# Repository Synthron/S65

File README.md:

# S65xx Computer System

Yet another 8bit Retro Computer

Completely bloated, overkill and fully hackable!

## ToDo

- [x] Finish Hardware
- Software
  - [ ] WozMon
    - [x] Implement Serial IO
    - [x] Implement Input Buffer
    - [ ] extended for block write
  - [ ] Kernel Functions
    - [ ] General SysCalls
    - [ ] Hardware Drivers
  - [x] RAM-Kernel
  - [x] Basic
  - [x] EhBasic
  - [ ] File System
  - [ ] Operating System
- Hardware
  - [ ] order PCBs
  - [ ] order parts
  - [ ] solder together

## Hardware

- Modules
  - [x] Backplane Bus
  - [x] CPU
  - [x] ROM
  - [x] RAM
  - [x] Bank/IRQ
  - [x] LCD/IRQ
  - [x] SIO
  - [x] PIO
  - [x] User Ports
  - [x] IDE
  - [x] Simple-IDE
  - [x] CF
  - [x] SID
  - [x] Addr + RTC + Clock
  - [x] Prototyping Board
  - [x] LPT Interface
  - [x] MyCPU Graphics Unit Interface

## Software Brainstorm

- EhBasic
  - maybe Microsoft Basic? See Ben Eater
    - both in different banks
- WozMon Main Boot
- Serial Program Bootloader
- File System (FAT?)
- DOS-Like UI

boot routine:

- selftest
  - RAM Check
  - ROM Check + version
- Load Kernel functions to RAM
- Start Monitor

## Memory Map

General:

| Start | End  | Usage      | Size   |
|-------|------|------------|--------|
| 0000  | 7FFF | RAM        | 32.768 |
| 8000  | BEFF | RAM Banked | 16.128 |
| BF00  | BFFF | IO Space   |    256 |
| C000  | FFFF | ROM Banked | 16.384 |

IO Space:

| Start | End  | Usage         |Size|
|-------|------|---------------|----|
| BF00  | BF07 | Bank & IRQ    | 8  |
| BF08  | BF0F | TPI IDE       | 8  |
| BF10  | BF12 | LPT           | 2  |
| BF13  | BF14 | --- (LPT2)    | 2  |
| BF14  | BF16 | MyCPU VGA     | 3  |
| BF17  | BF1B | ---           | 5  |
| BF1C  | BF1F | PIA LEDs      | 4  |
| BF20  | BF2F | VIA 1 LCD IRQ | 16 |
| BF30  | BF3F | VIA 2         | 16 |
| BF40  | BF4F | VIA 3         | 16 |
| BF50  | BF53 | ACIA 1        | 4  |
| BF54  | BF57 | ACIA 2        | 4  |
| BF58  | BF5B | --- (ACIA 3)  | 4  |
| BF5C  | BF5F | --- (ACIA 4)  | 4  |
| BF60  | BF7F | SID 8580      | 32 |
| BF80  | BF87 | Simple IDE    | 8  |
| BF88  | BF8F | CF Card       | 8  |
| BF90  | BF9F | RTC           | 16 |
| BFA0  | BFFF | ---           | 96 |

## Interrupts

The TPI Chip for the memory banks also functions as a priority interrupt controller, providing 5 seperate interrupt lines.  
IRQ_0 is further divided into 8 lines for communication modules, giving an overall of 14 available IRQ-Lines.  

These are currently used as follows:

- IRQ -> TPI
  - IRQ_0 -> VIA0
    - IRQ_0.0 -> ACIA0
    - IRQ_0.1 -> ACIA1
    - IRQ_0.2 -> ACIA2
    - IRQ_0.3 -> ACIA3
    - IRQ_0.4 -> RTC
    - IRQ_0.5 -> ---
    - IRQ_0.6 -> ---
    - IRQ_0.7 -> ---
  - IRQ_1 -> VIA1
  - IRQ_2 -> VIA2
  - IRQ_3 -> ---
  - IRQ_4 -> ---
- NMI -> ---

Note that the NMI is connected to a push button on the bus board.

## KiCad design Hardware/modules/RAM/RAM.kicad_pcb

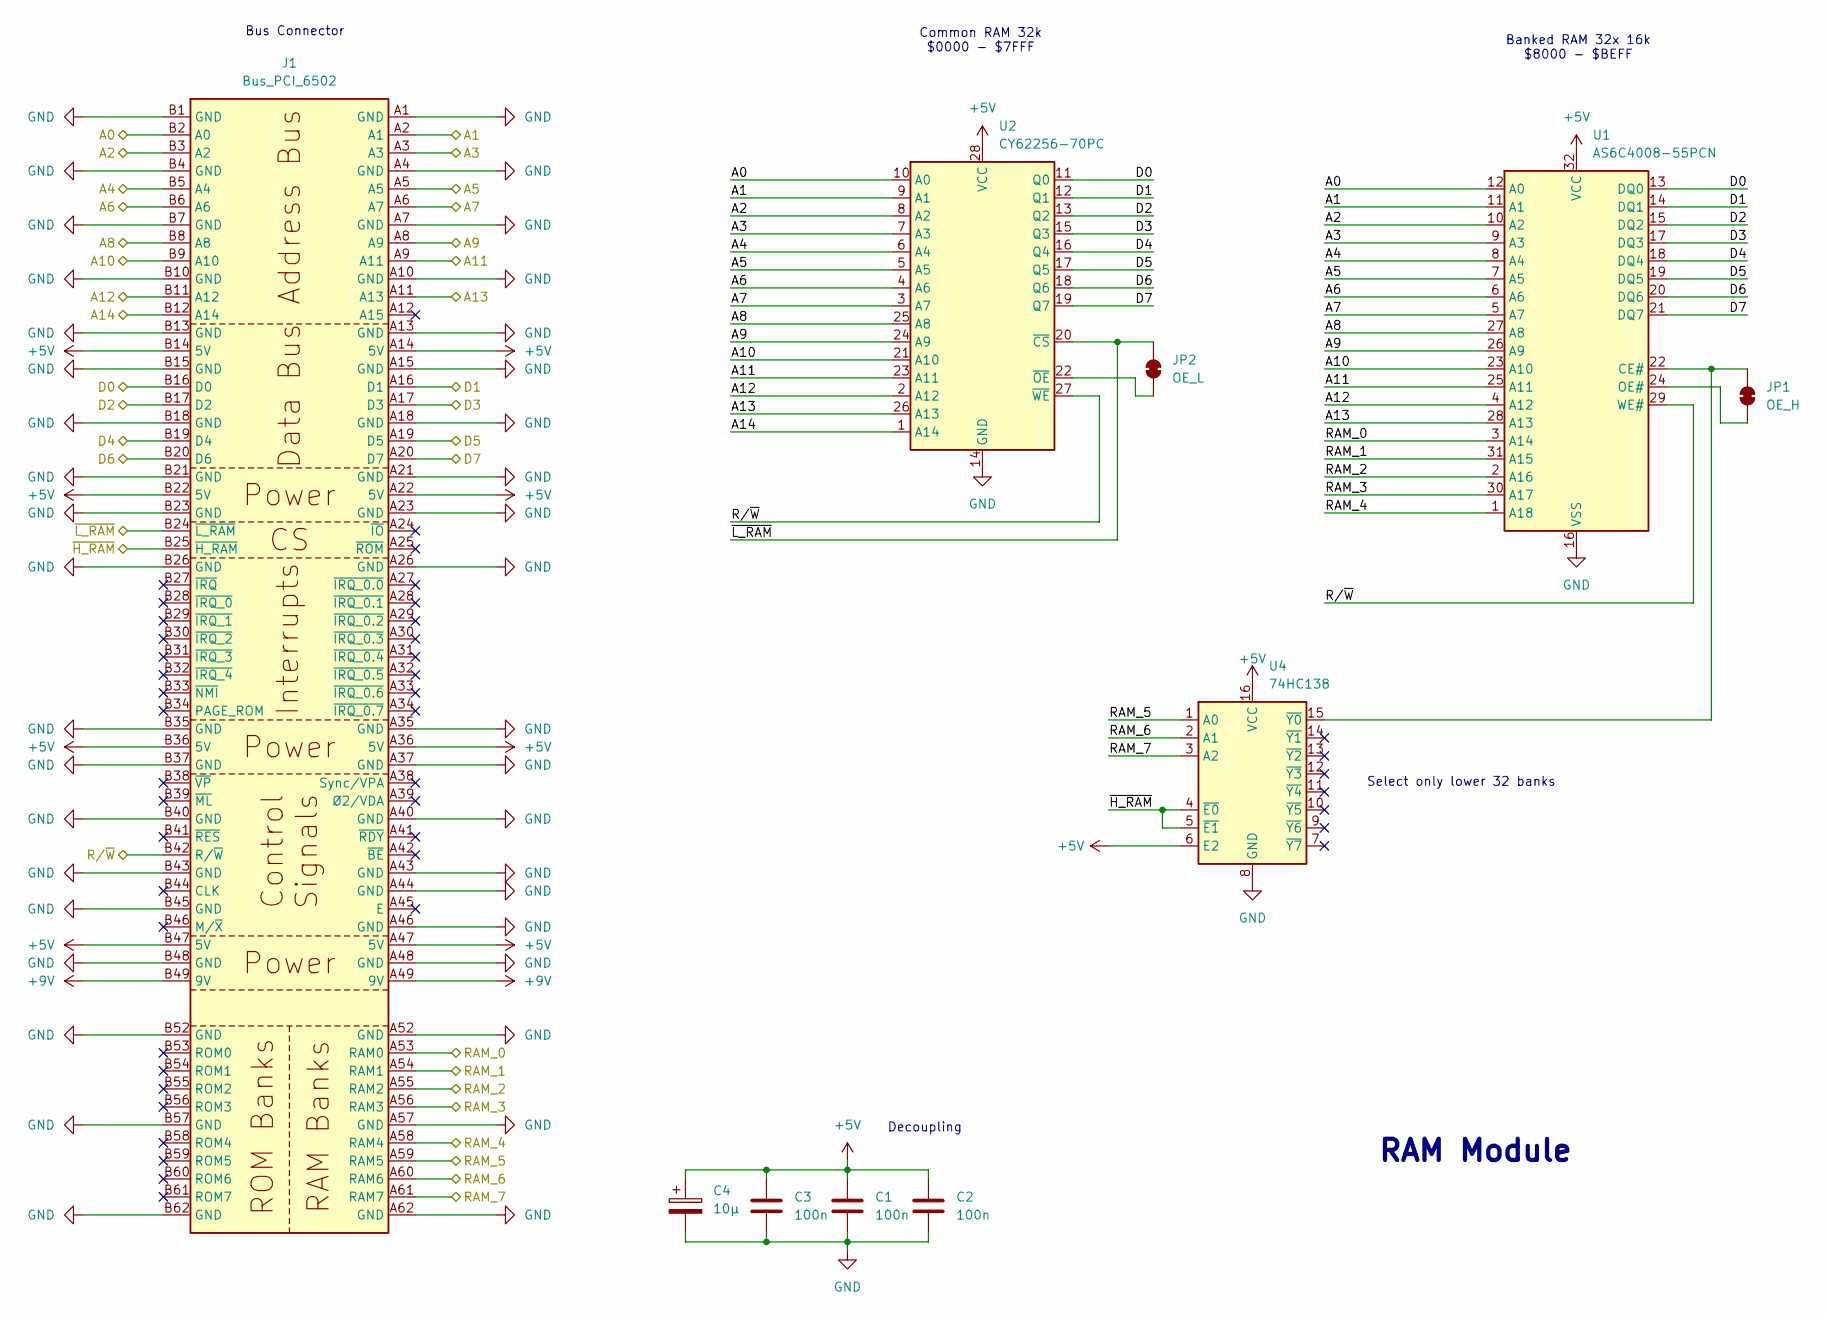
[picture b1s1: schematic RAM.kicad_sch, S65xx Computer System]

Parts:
C1, C2, C3: 100n; C_0805_2012Metric
C4: 10µ; CP_Radial_D5.0mm_P2.50mm
J1: Bus_PCI_6502; BUS_PCI
JP1: OE_H; SolderJumper-2_P1.3mm_Bridged_RoundedPad1.0x1.5mm
JP2: OE_L; SolderJumper-2_P1.3mm_Bridged_RoundedPad1.0x1.5mm
U1: AS6C4008-55PCN; DIP-32_W15.24mm
U2: CY62256-70PC; DIP-28_W15.24mm
U4: 74HC138; DIP-16_W7.62mm

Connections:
+5V: C1.1, C2.1, C3.1, C4.1, J1.A14 (5V), J1.A22 (5V), J1.A36 (5V), J1.A47 (5V), J1.B14 (5V), J1.B22 (5V), J1.B36 (5V), J1.B47 (5V), U1.32 (VCC), U2.28 (VCC), U4.6 (E2), U4.16 (VCC)
+9V: J1.A49 (9V), J1.B49 (9V)
/A0: J1.B2 (A0), U1.12 (A0), U2.10 (A0)
/A1: J1.A2 (A1), U1.11 (A1), U2.9 (A1)
/A2: J1.B3 (A2), U1.10 (A2), U2.8 (A2)
/A3: J1.A3, U1.9 (A3), U2.7 (A3)
/A4: J1.B5 (A4), U1.8 (A4), U2.6 (A4)
/A5: J1.A5, U1.7 (A5), U2.5 (A5)
/A6: J1.B6 (A6), U1.6 (A6), U2.4 (A6)
/A7: J1.A6 (A7), U1.5 (A7), U2.3 (A7)
/A8: J1.B8 (A8), U1.27 (A8), U2.25 (A8)
/A9: J1.A8 (A9), U1.26 (A9), U2.24 (A9)
/A10: J1.B9 (A10), U1.23 (A10), U2.21 (A10)
/A11: J1.A9 (A11), U1.25 (A11), U2.23 (A11)
/A12: J1.B11 (A12), U1.4 (A12), U2.2 (A12)
/A13: J1.A11 (A13), U1.28 (A13), U2.26 (A13)
/A14: J1.B12 (A14), U2.1 (A14)
/D0: J1.B16 (D0), U1.13 (DQ0), U2.11 (Q0)
/D1: J1.A16 (D1), U1.14 (DQ1), U2.12 (Q1)
/D2: J1.B17 (D2), U1.15 (DQ2), U2.13 (Q2)
/D3: J1.A17 (D3), U1.17 (DQ3), U2.15 (Q3)
/D4: J1.B19 (D4), U1.18 (DQ4), U2.16 (Q4)
/D5: J1.A19 (D5), U1.19 (DQ5), U2.17 (Q5)
/D6: J1.B20 (D6), U1.20 (DQ6), U2.18 (Q6)
/D7: J1.A20 (D7), U1.21 (DQ7), U2.19 (Q7)
/RAM_0: J1.A53 (RAM0), U1.3 (A14)
/RAM_1: J1.A54 (RAM1), U1.31 (A15)
/RAM_2: J1.A55 (RAM2), U1.2 (A16)
/RAM_3: J1.A56 (RAM3), U1.30 (A17)
/RAM_4: J1.A58 (RAM4), U1.1 (A18)
/RAM_5: J1.A59 (RAM5), U4.1 (A0)
/RAM_6: J1.A60 (RAM6), U4.2 (A1)
/RAM_7: J1.A61 (RAM7), U4.3 (A2)
/R/~W: J1.B42 (R/~W), U1.29 (WE#), U2.27 (~WE)
/~H_RAM: J1.B25 (~H_RAM), U4.4 (~E0), U4.5 (~E1)
/~L_RAM: J1.B24 (~L_RAM), JP2.2 (B), U2.20 (~CS)
GND: C1.2, C2.2, C3.2, C4.2, J1.A1 (GND), J1.A4 (GND), J1.A7 (GND), J1.A10 (GND), J1.A13 (GND), J1.A15 (GND), J1.A18 (GND), J1.A21 (GND), J1.A23 (GND), J1.A26 (GND), J1.A35 (GND), J1.A37 (GND), J1.A40 (GND), J1.A43 (GND), J1.A44 (GND), J1.A46 (GND), J1.A48 (GND), J1.A52 (GND), J1.A57 (GND), J1.A62 (GND), J1.B1 (GND), J1.B4 (GND), J1.B7 (GND), J1.B10 (GND), J1.B13 (GND), J1.B15 (GND), J1.B18 (GND), J1.B21 (GND), J1.B23 (GND), J1.B26 (GND), J1.B35 (GND), J1.B37 (GND), J1.B40 (GND), J1.B43 (GND), J1.B45 (GND), J1.B48 (GND), J1.B52 (GND), J1.B57 (GND), J1.B62 (GND), U1.16 (VSS), U2.14 (GND), U4.8 (GND)
unnamed: JP1.1 (A), U1.24 (OE#)
unnamed: JP1.2 (B), U1.22 (CE#), U4.15 (~Y0)
unnamed: JP2.1 (A), U2.22 (~OE)

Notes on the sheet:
Common RAM 32k $0000 - $7FFF
RAM Module
Bus Connector
Select only lower 32 banks
Decoupling
Banked RAM 32x 16k $8000 - $BEFF

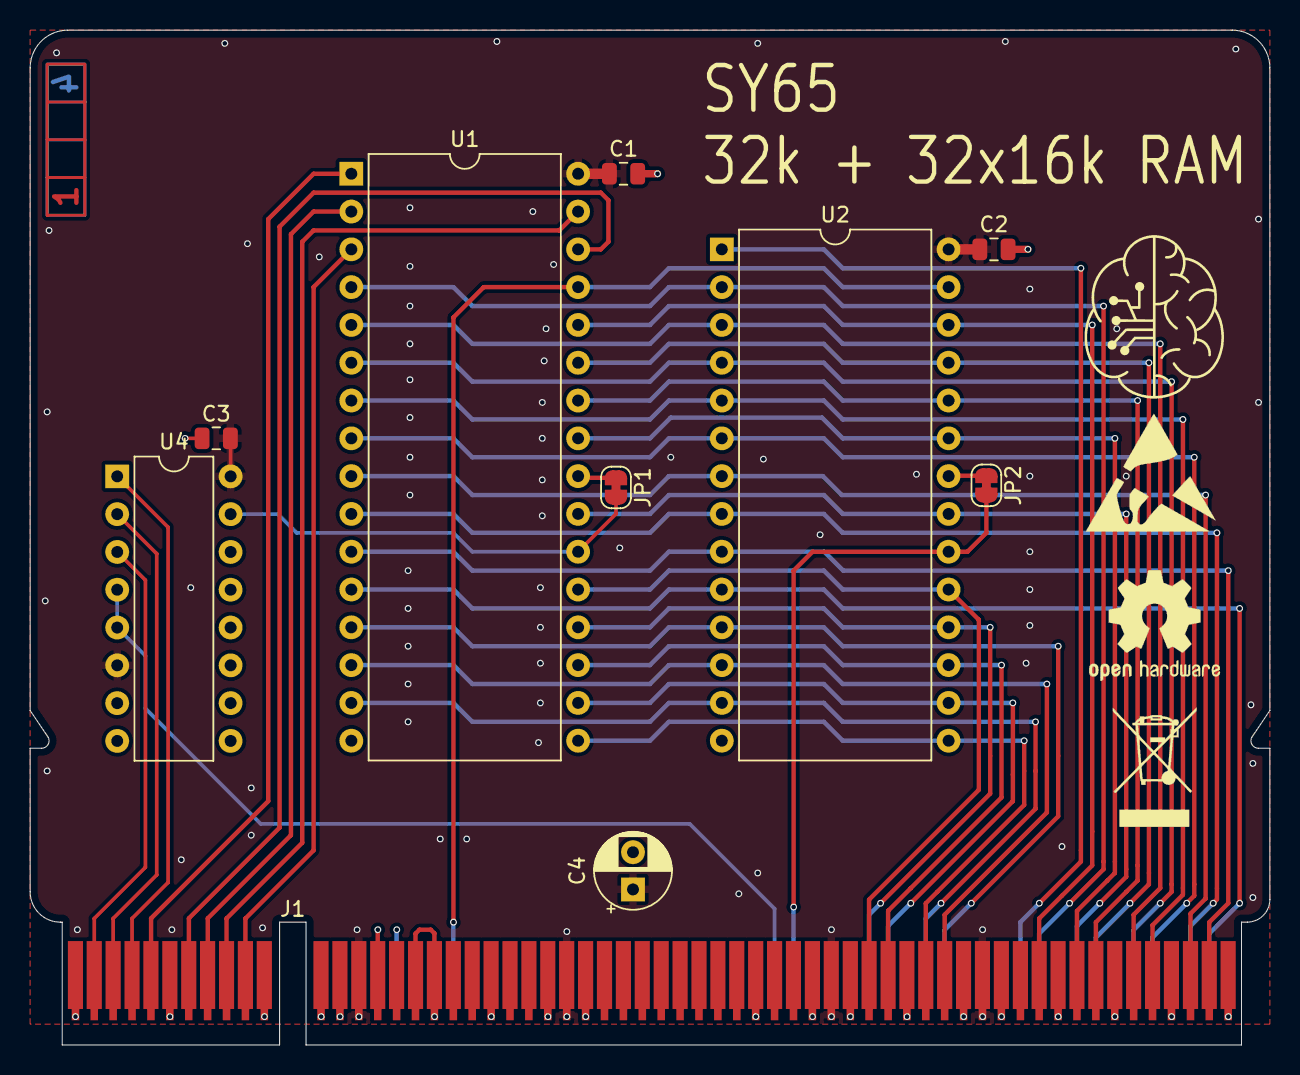
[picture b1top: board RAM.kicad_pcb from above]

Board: 4 copper layers, 83.3 x 68.2 mm, 11 parts (1 on the bottom side), 40 nets.

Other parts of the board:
Ref**: Val**; ladder_4

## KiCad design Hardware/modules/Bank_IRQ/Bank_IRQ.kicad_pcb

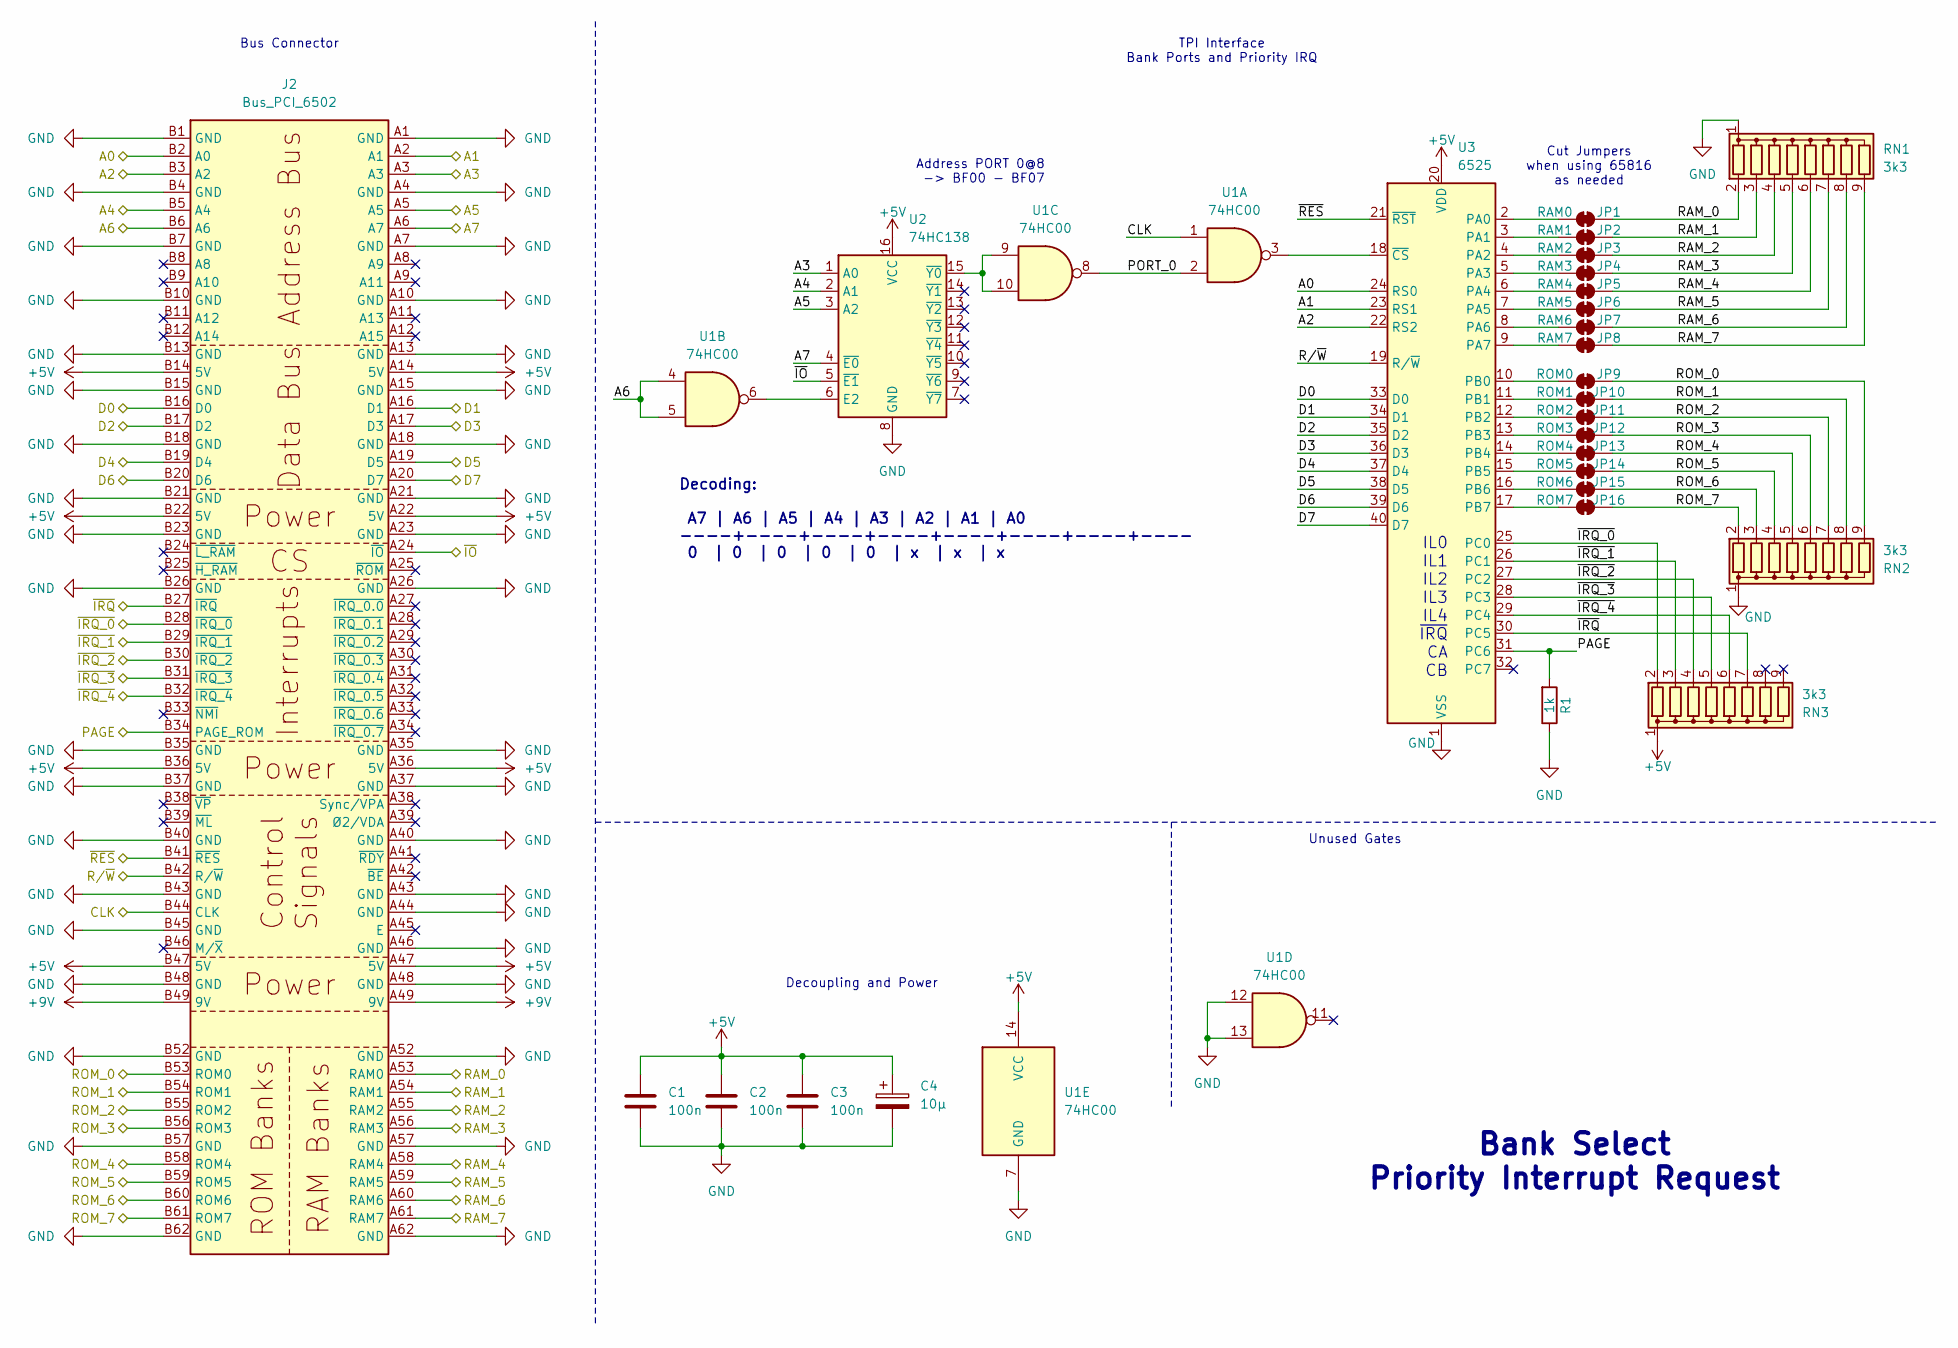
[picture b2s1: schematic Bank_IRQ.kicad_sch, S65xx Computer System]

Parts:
C1, C2, C3: 100n; C_0805_2012Metric
C4: 10µ; CP_Radial_D5.0mm_P2.50mm
J2: Bus_PCI_6502; BUS_PCI
JP1: RAM0; SolderJumper-2_P1.3mm_Bridged_RoundedPad1.0x1.5mm
JP2: RAM1; SolderJumper-2_P1.3mm_Bridged_RoundedPad1.0x1.5mm
JP3: RAM2; SolderJumper-2_P1.3mm_Bridged_RoundedPad1.0x1.5mm
JP4: RAM3; SolderJumper-2_P1.3mm_Bridged_RoundedPad1.0x1.5mm
JP5: RAM4; SolderJumper-2_P1.3mm_Bridged_RoundedPad1.0x1.5mm
JP6: RAM5; SolderJumper-2_P1.3mm_Bridged_RoundedPad1.0x1.5mm
JP7: RAM6; SolderJumper-2_P1.3mm_Bridged_RoundedPad1.0x1.5mm
JP8: RAM7; SolderJumper-2_P1.3mm_Bridged_RoundedPad1.0x1.5mm
JP9: ROM0; SolderJumper-2_P1.3mm_Bridged_RoundedPad1.0x1.5mm
JP10: ROM1; SolderJumper-2_P1.3mm_Bridged_RoundedPad1.0x1.5mm
JP11: ROM2; SolderJumper-2_P1.3mm_Bridged_RoundedPad1.0x1.5mm
JP12: ROM3; SolderJumper-2_P1.3mm_Bridged_RoundedPad1.0x1.5mm
JP13: ROM4; SolderJumper-2_P1.3mm_Bridged_RoundedPad1.0x1.5mm
JP14: ROM5; SolderJumper-2_P1.3mm_Bridged_RoundedPad1.0x1.5mm
JP15: ROM6; SolderJumper-2_P1.3mm_Bridged_RoundedPad1.0x1.5mm
JP16: ROM7; SolderJumper-2_P1.3mm_Bridged_RoundedPad1.0x1.5mm
R1: 1k; R_0805_2012Metric
RN1, RN2, RN3: 3k3; R_Array_SIP9
U1: 74HC00; DIP-14_W7.62mm_LongPads
U2: 74HC138; DIP-16_W7.62mm_LongPads
U3: 6525; DIP-40_W15.24mm

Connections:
+5V: C1.1, C2.1, C3.1, C4.1, J2.A14 (5V), J2.A22 (5V), J2.A36 (5V), J2.A47 (5V), J2.B14 (5V), J2.B22 (5V), J2.B36 (5V), J2.B47 (5V), RN3.1 (common), U1.14 (VCC), U2.16 (VCC), U3.20 (VDD)
+9V: J2.A49 (9V), J2.B49 (9V)
/A0: J2.B2 (A0), U3.24 (RS0)
/A1: J2.A2 (A1), U3.23 (RS1)
/A2: J2.B3 (A2), U3.22 (RS2)
/A3: J2.A3, U2.1 (A0)
/A4: J2.B5 (A4), U2.2 (A1)
/A5: J2.A5, U2.3 (A2)
/A6: J2.B6 (A6), U1.4, U1.5
/A7: J2.A6 (A7), U2.4 (~E0)
/CLK: J2.B44 (CLK), U1.1
/D0: J2.B16 (D0), U3.33 (D0)
/D1: J2.A16 (D1), U3.34 (D1)
/D2: J2.B17 (D2), U3.35 (D2)
/D3: J2.A17 (D3), U3.36 (D3)
/D4: J2.B19 (D4), U3.37 (D4)
/D5: J2.A19 (D5), U3.38 (D5)
/D6: J2.B20 (D6), U3.39 (D6)
/D7: J2.A20 (D7), U3.40 (D7)
/PAGE: J2.B34 (PAGE_ROM), R1.2, U3.31 (PC6)
/PORT_0: U1.2, U1.8
/RAM_0: J2.A53 (RAM0), JP1.2 (B), RN1.2 (R1)
/RAM_1: J2.A54 (RAM1), JP2.2 (B), RN1.3 (R2)
/RAM_2: J2.A55 (RAM2), JP3.2 (B), RN1.4 (R3)
/RAM_3: J2.A56 (RAM3), JP4.2 (B), RN1.5 (R4)
/RAM_4: J2.A58 (RAM4), JP5.2 (B), RN1.6 (R5)
/RAM_5: J2.A59 (RAM5), JP6.2 (B), RN1.7 (R6)
/RAM_6: J2.A60 (RAM6), JP7.2 (B), RN1.8 (R7)
/RAM_7: J2.A61 (RAM7), JP8.2 (B), RN1.9 (R8)
/ROM_0: J2.B53 (ROM0), JP9.2 (B), RN2.9 (R8)
/ROM_1: J2.B54 (ROM1), JP10.2 (B), RN2.8 (R7)
/ROM_2: J2.B55 (ROM2), JP11.2 (B), RN2.7 (R6)
/ROM_3: J2.B56 (ROM3), JP12.2 (B), RN2.6 (R5)
/ROM_4: J2.B58 (ROM4), JP13.2 (B), RN2.5 (R4)
/ROM_5: J2.B59 (ROM5), JP14.2 (B), RN2.4 (R3)
/ROM_6: J2.B60 (ROM6), JP15.2 (B), RN2.3 (R2)
/ROM_7: J2.B61 (ROM7), JP16.2 (B), RN2.2 (R1)
/R/~W: J2.B42 (R/~W), U3.19 (R/~W)
/~IO: J2.A24 (~IO), U2.5 (~E1)
/~IRQ_0: J2.B28 (~IRQ_0), RN3.2 (R1), U3.25 (PC0)
/~IRQ_1: J2.B29 (~IRQ_1), RN3.3 (R2), U3.26 (PC1)
/~IRQ_2: J2.B30 (~IRQ_2), RN3.4 (R3), U3.27 (PC2)
/~IRQ_3: J2.B31 (~IRQ_3), RN3.5 (R4), U3.28 (PC3)
/~IRQ_4: J2.B32 (~IRQ_4), RN3.6 (R5), U3.29 (PC4)
/~IRQ: J2.B27 (~IRQ), RN3.7 (R6), U3.30 (PC5)
/~RES: J2.B41 (~RES), U3.21 (~RST)
GND: C1.2, C2.2, C3.2, C4.2, J2.A1 (GND), J2.A4 (GND), J2.A7 (GND), J2.A10 (GND), J2.A13 (GND), J2.A15 (GND), J2.A18 (GND), J2.A21 (GND), J2.A23 (GND), J2.A26 (GND), J2.A35 (GND), J2.A37 (GND), J2.A40 (GND), J2.A43 (GND), J2.A44 (GND), J2.A46 (GND), J2.A48 (GND), J2.A52 (GND), J2.A57 (GND), J2.A62 (GND), J2.B1 (GND), J2.B4 (GND), J2.B7 (GND), J2.B10 (GND), J2.B13 (GND), J2.B15 (GND), J2.B18 (GND), J2.B21 (GND), J2.B23 (GND), J2.B26 (GND), J2.B35 (GND), J2.B37 (GND), J2.B40 (GND), J2.B43 (GND), J2.B45 (GND), J2.B48 (GND), J2.B52 (GND), J2.B57 (GND), J2.B62 (GND), R1.1, RN1.1 (common), RN2.1 (common), U1.7 (GND), U1.12, U1.13, U2.8 (GND), U3.1 (VSS)
unnamed: JP1.1 (A), U3.2 (PA0)
unnamed: JP2.1 (A), U3.3 (PA1)
unnamed: JP3.1 (A), U3.4 (PA2)
unnamed: JP4.1 (A), U3.5 (PA3)
unnamed: JP5.1 (A), U3.6 (PA4)
unnamed: JP6.1 (A), U3.7 (PA5)
unnamed: JP7.1 (A), U3.8 (PA6)
unnamed: JP8.1 (A), U3.9 (PA7)
unnamed: JP9.1 (A), U3.10 (PB0)
unnamed: JP10.1 (A), U3.11 (PB1)
unnamed: JP11.1 (A), U3.12 (PB2)
unnamed: JP12.1 (A), U3.13 (PB3)
unnamed: JP13.1 (A), U3.14 (PB4)
unnamed: JP14.1 (A), U3.15 (PB5)
unnamed: JP15.1 (A), U3.16 (PB6)
unnamed: JP16.1 (A), U3.17 (PB7)
unnamed: U1.6, U2.6 (E2)
unnamed: U1.9, U1.10, U2.15 (~Y0)
unnamed: U1.3, U3.18 (~CS)

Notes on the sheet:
Decoding: A7 | A6 | A5 | A4 | A3 | A2 | A1 | A0 ----+----+----+----+----+----+----+---- 0 | 0 | 0 | 0 | 0 | x | x | x
Bus Connector
Cut Jumpers when using 65816 as needed
Bank Select Priority Interrupt Request
TPI Interface Bank Ports and Priority IRQ
Decoupling and Power
Unused Gates
Address PORT 0@8 -> BF00 - BF07
IL0 IL1 IL2 IL3 IL4 ~{IRQ} CA CB

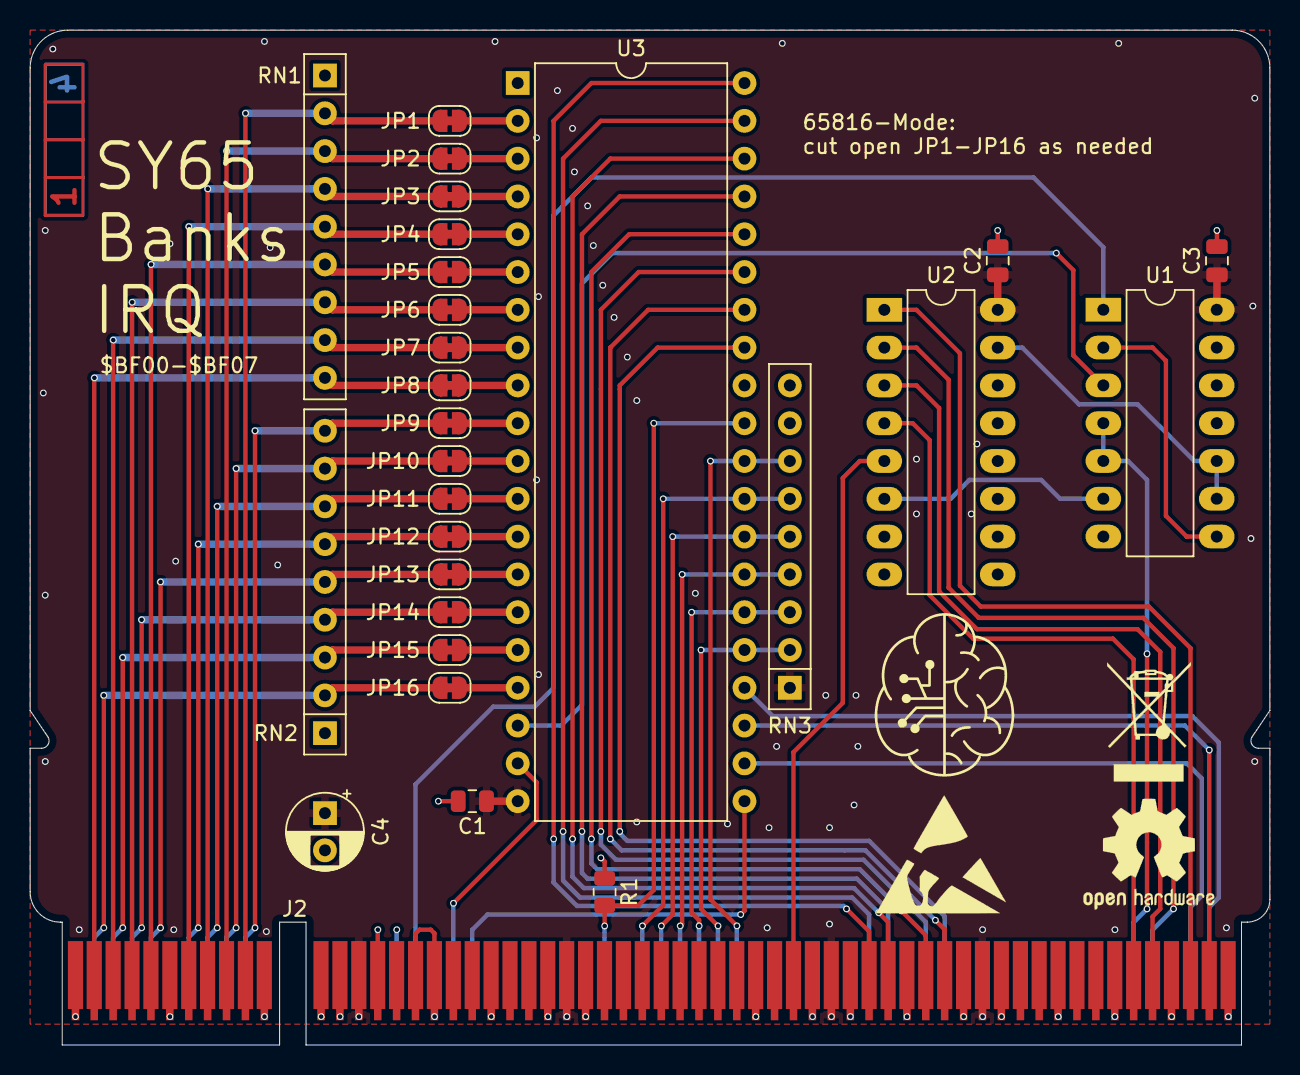
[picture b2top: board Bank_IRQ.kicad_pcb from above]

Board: 4 copper layers, 83.3 x 68.2 mm, 29 parts (1 on the bottom side), 66 nets.

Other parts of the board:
Ref**: Val**; ladder_4

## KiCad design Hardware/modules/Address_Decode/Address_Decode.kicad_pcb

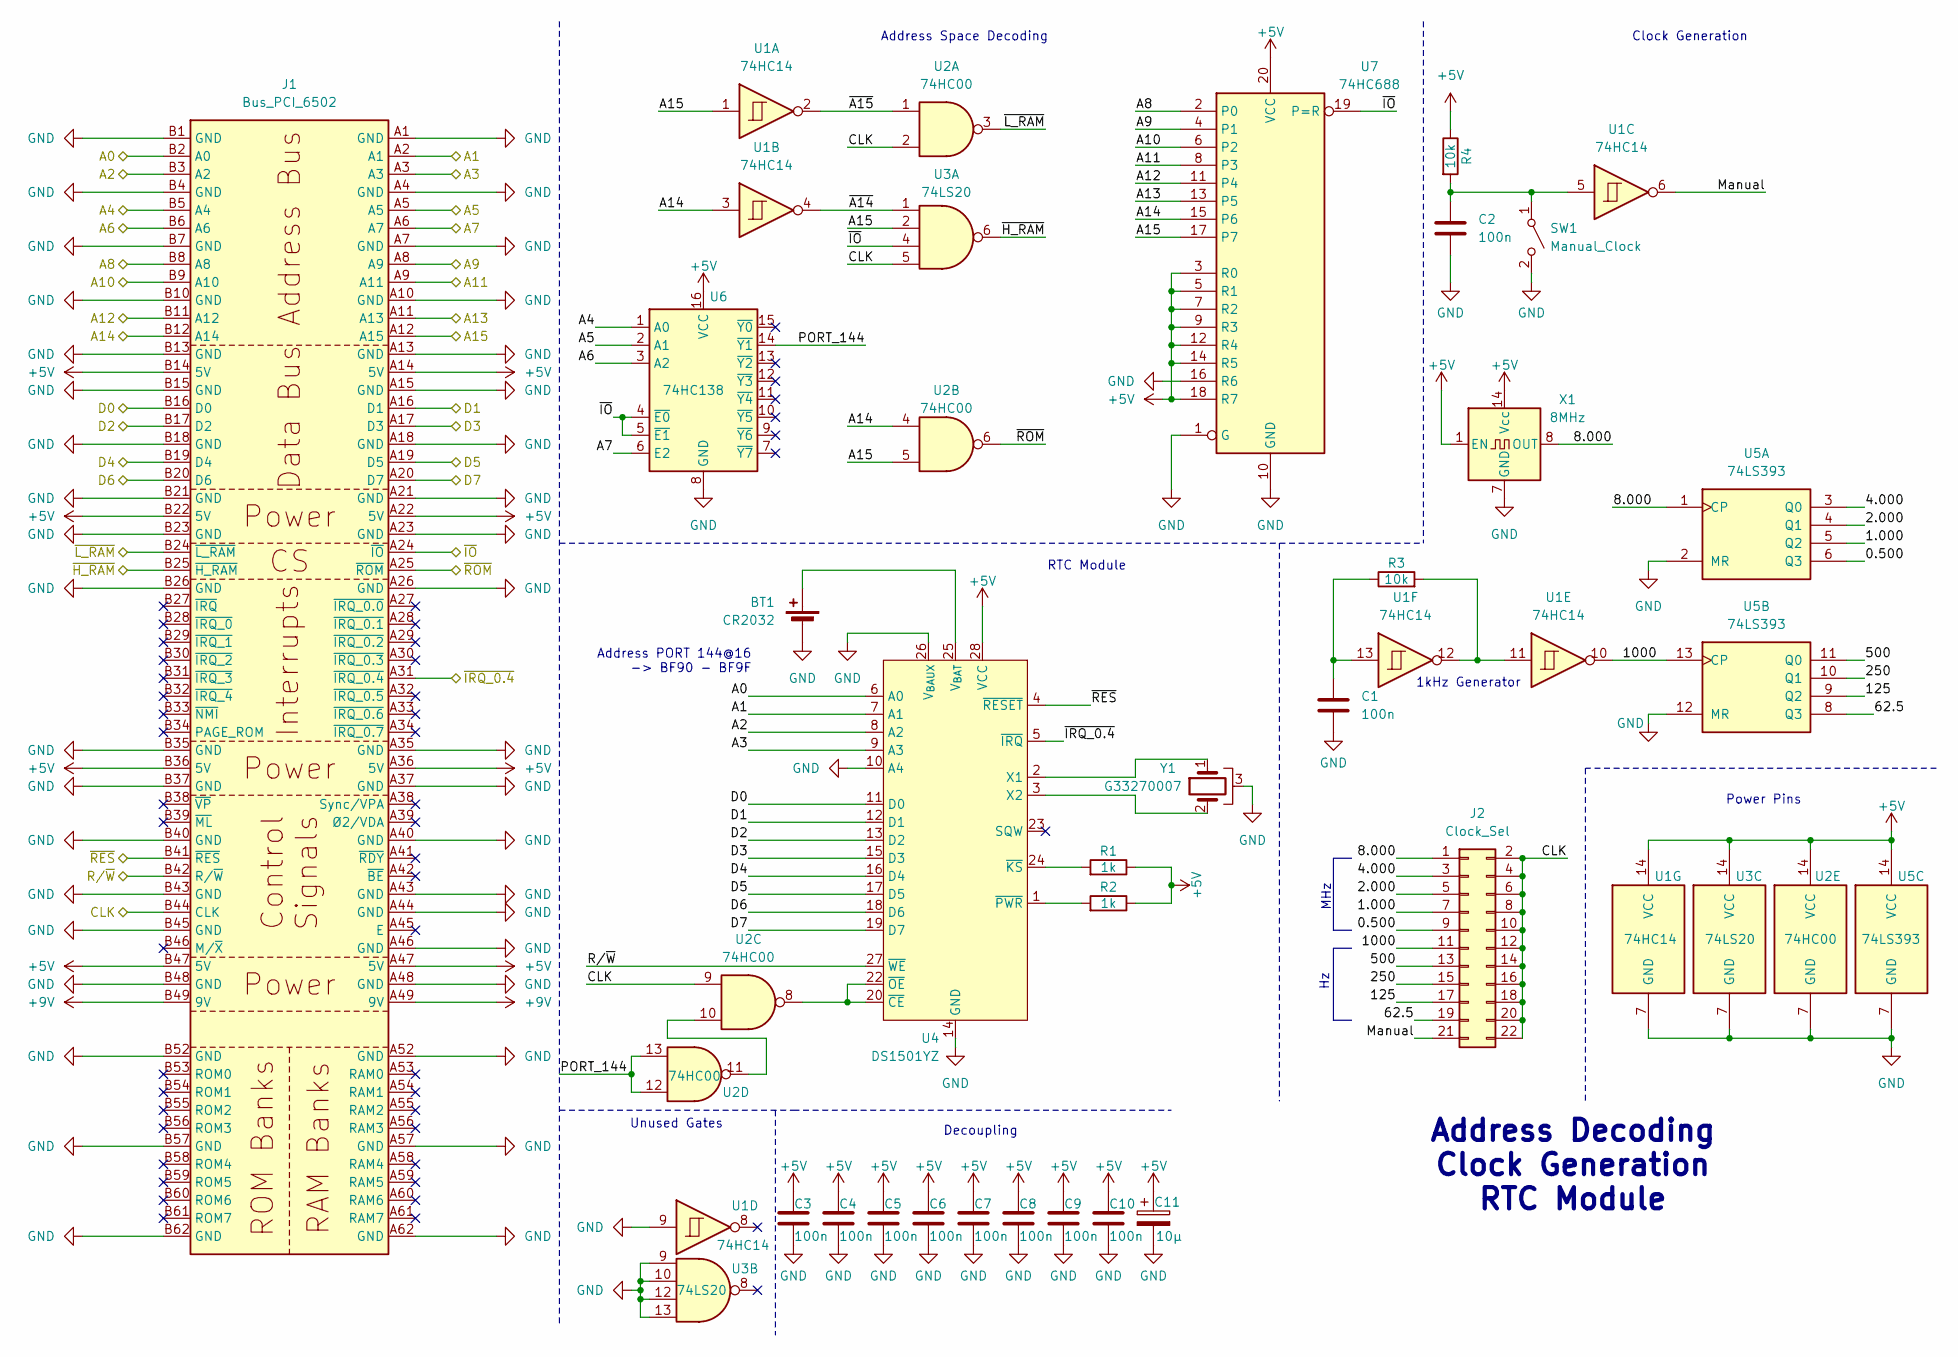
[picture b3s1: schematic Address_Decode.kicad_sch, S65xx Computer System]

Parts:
BT1: CR2032; BatteryHolder_Keystone_3002_1x2032
C1, C2, C3, C4, C5, C6, C7, C8, C9, C10: 100n; C_0805_2012Metric
C11: 10µ; CP_Radial_D5.0mm_P2.50mm
J1: Bus_PCI_6502; BUS_PCI
J2: Clock_Sel; PinHeader_2x11_P2.54mm_Horizontal
R1, R2: 1k; R_0805_2012Metric
R3, R4: 10k; R_0805_2012Metric
SW1: Manual_Clock; SPST_Edge
U1: 74HC14; DIP-14_W7.62mm_LongPads
U2: 74HC00; DIP-14_W7.62mm_LongPads
U3: 74LS20; DIP-14_W7.62mm_LongPads
U4: DS1501YZ; SOP-28_8.4x18.16mm_P1.27mm
U5: 74LS393; DIP-14_W7.62mm_LongPads
U6: 74HC138; DIP-16_W7.62mm_LongPads
U7: 74HC688; DIP-20_W7.62mm_LongPads
X1: 8MHz; Oscillator_DIP-14
Y1: G33270007; Crystal_SMD_FrontierElectronics_FM206

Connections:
+5V: C3.1, C4.1, C5.1, C6.1, C7.1, C8.1, C9.1, C10.1, C11.1, J1.A14 (5V), J1.A22 (5V), J1.A36 (5V), J1.A47 (5V), J1.B14 (5V), J1.B22 (5V), J1.B36 (5V), J1.B47 (5V), R1.1, R2.1, R4.1, U1.14 (VCC), U2.14 (VCC), U3.14 (VCC), U4.28 (VCC), U5.14 (VCC), U6.16 (VCC), U7.3 (R0), U7.5 (R1), U7.7 (R2), U7.9 (R3), U7.12 (R4), U7.14 (R5), U7.18 (R7), U7.20 (VCC), X1.1 (EN), X1.14 (Vcc)
+9V: J1.A49 (9V), J1.B49 (9V)
/0.500: J2.9, U5.6 (Q3)
/1.000: J2.7, U5.5 (Q2)
/2.000: J2.5, U5.4 (Q1)
/4.000: J2.3, U5.3 (Q0)
/8.000: J2.1, U5.1 (CP), X1.8 (OUT)
/62.5: J2.19, U5.8 (Q3)
/125: J2.17, U5.9 (Q2)
/250: J2.15, U5.10 (Q1)
/500: J2.13, U5.11 (Q0)
/1000: J2.11, U1.10, U5.13 (CP)
/A0: J1.B2 (A0), U4.6 (A0)
/A1: J1.A2 (A1), U4.7 (A1)
/A2: J1.B3 (A2), U4.8 (A2)
/A3: J1.A3, U4.9 (A3)
/A4: J1.B5 (A4), U6.1 (A0)
/A5: J1.A5, U6.2 (A1)
/A6: J1.B6 (A6), U6.3 (A2)
/A7: J1.A6 (A7), U6.6 (E2)
/A8: J1.B8 (A8), U7.2 (P0)
/A9: J1.A8 (A9), U7.4 (P1)
/A10: J1.B9 (A10), U7.6 (P2)
/A11: J1.A9 (A11), U7.8 (P3)
/A12: J1.B11 (A12), U7.11 (P4)
/A13: J1.A11 (A13), U7.13 (P5)
/A14: J1.B12 (A14), U1.3, U2.4, U7.15 (P6)
/A15: J1.A12 (A15), U1.1, U2.5, U3.2, U7.17 (P7)
/CLK: J1.B44 (CLK), J2.2, J2.4, J2.6, J2.8, J2.10, J2.12, J2.14, J2.16, J2.18, J2.20, J2.22, U2.2, U2.9, U3.5
/D0: J1.B16 (D0), U4.11 (D0)
/D1: J1.A16 (D1), U4.12 (D1)
/D2: J1.B17 (D2), U4.13 (D2)
/D3: J1.A17 (D3), U4.15 (D3)
/D4: J1.B19 (D4), U4.16 (D4)
/D5: J1.A19 (D5), U4.17 (D5)
/D6: J1.B20 (D6), U4.18 (D6)
/D7: J1.A20 (D7), U4.19 (D7)
/Manual: J2.21, U1.6
/PORT_144: U2.12, U2.13, U6.14 (~Y1)
/R/~W: J1.B42 (R/~W), U4.27 (~WE)
/~A14: U1.4, U3.1
/~A15: U1.2, U2.1
/~H_RAM: J1.B25 (~H_RAM), U3.6
/~IO: J1.A24 (~IO), U3.4, U6.4 (~E0), U6.5 (~E1), U7.19 (P=R)
/~IRQ_0.4: J1.A31 (~IRQ_0.4), U4.5 (~IRQ)
/~L_RAM: J1.B24 (~L_RAM), U2.3
/~RES: J1.B41 (~RES), U4.4 (~RESET)
/~ROM: J1.A25 (~ROM), U2.6
GND: BT1.2 (-), C1.2, C2.2, C3.2, C4.2, C5.2, C6.2, C7.2, C8.2, C9.2, C10.2, C11.2, J1.A1 (GND), J1.A4 (GND), J1.A7 (GND), J1.A10 (GND), J1.A13 (GND), J1.A15 (GND), J1.A18 (GND), J1.A21 (GND), J1.A23 (GND), J1.A26 (GND), J1.A35 (GND), J1.A37 (GND), J1.A40 (GND), J1.A43 (GND), J1.A44 (GND), J1.A46 (GND), J1.A48 (GND), J1.A52 (GND), J1.A57 (GND), J1.A62 (GND), J1.B1 (GND), J1.B4 (GND), J1.B7 (GND), J1.B10 (GND), J1.B13 (GND), J1.B15 (GND), J1.B18 (GND), J1.B21 (GND), J1.B23 (GND), J1.B26 (GND), J1.B35 (GND), J1.B37 (GND), J1.B40 (GND), J1.B43 (GND), J1.B45 (GND), J1.B48 (GND), J1.B52 (GND), J1.B57 (GND), J1.B62 (GND), SW1.2 (B), U1.7 (GND), U1.9, U2.7 (GND), U3.7 (GND), U3.9, U3.10, U3.12, U3.13, U4.10 (A4), U4.14 (GND), U4.21 (GND), U4.26 (V_{BAUX}), U5.2 (MR), U5.7 (GND), U5.12 (MR), U6.8 (GND), U7.1 (G), U7.10 (GND), U7.16 (R6), X1.7 (GND), Y1.3
unnamed: BT1.1 (+), U4.25 (V_{BAT})
unnamed: C1.1, R3.1, U1.13
unnamed: R3.2, U1.11, U1.12
unnamed: C2.1, R4.2, SW1.1 (A), U1.5
unnamed: U2.10, U2.11
unnamed: U4.2 (X1), Y1.1
unnamed: U4.3 (X2), Y1.2
unnamed: U2.8, U4.20 (~CE), U4.22 (~OE)
unnamed: R1.2, U4.24 (~KS)
unnamed: R2.2, U4.1 (~PWR)

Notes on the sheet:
Clock Generation
1kHz Generator
RTC Module
Address Decoding Clock Generation RTC Module
Power Pins
Address Space Decoding
MHz
Unused Gates
Address PORT 144@16 -> BF90 - BF9F
Decoupling

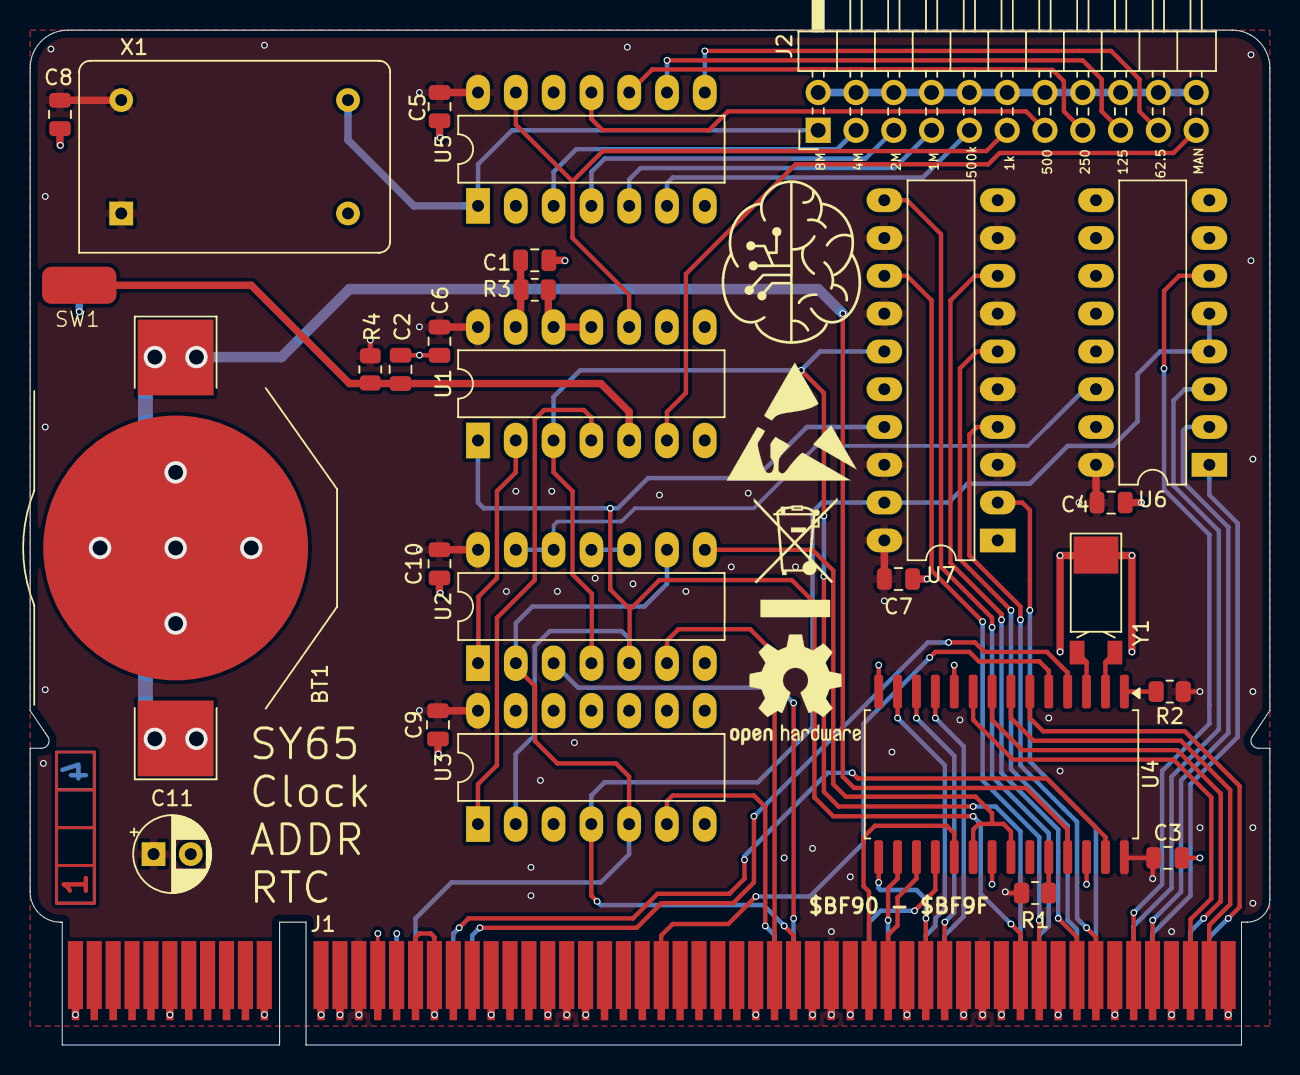
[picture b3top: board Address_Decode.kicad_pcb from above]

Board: 4 copper layers, 83.3 x 68.2 mm, 29 parts (1 on the bottom side), 59 nets.

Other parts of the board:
Ref**: Val**; ladder_4
